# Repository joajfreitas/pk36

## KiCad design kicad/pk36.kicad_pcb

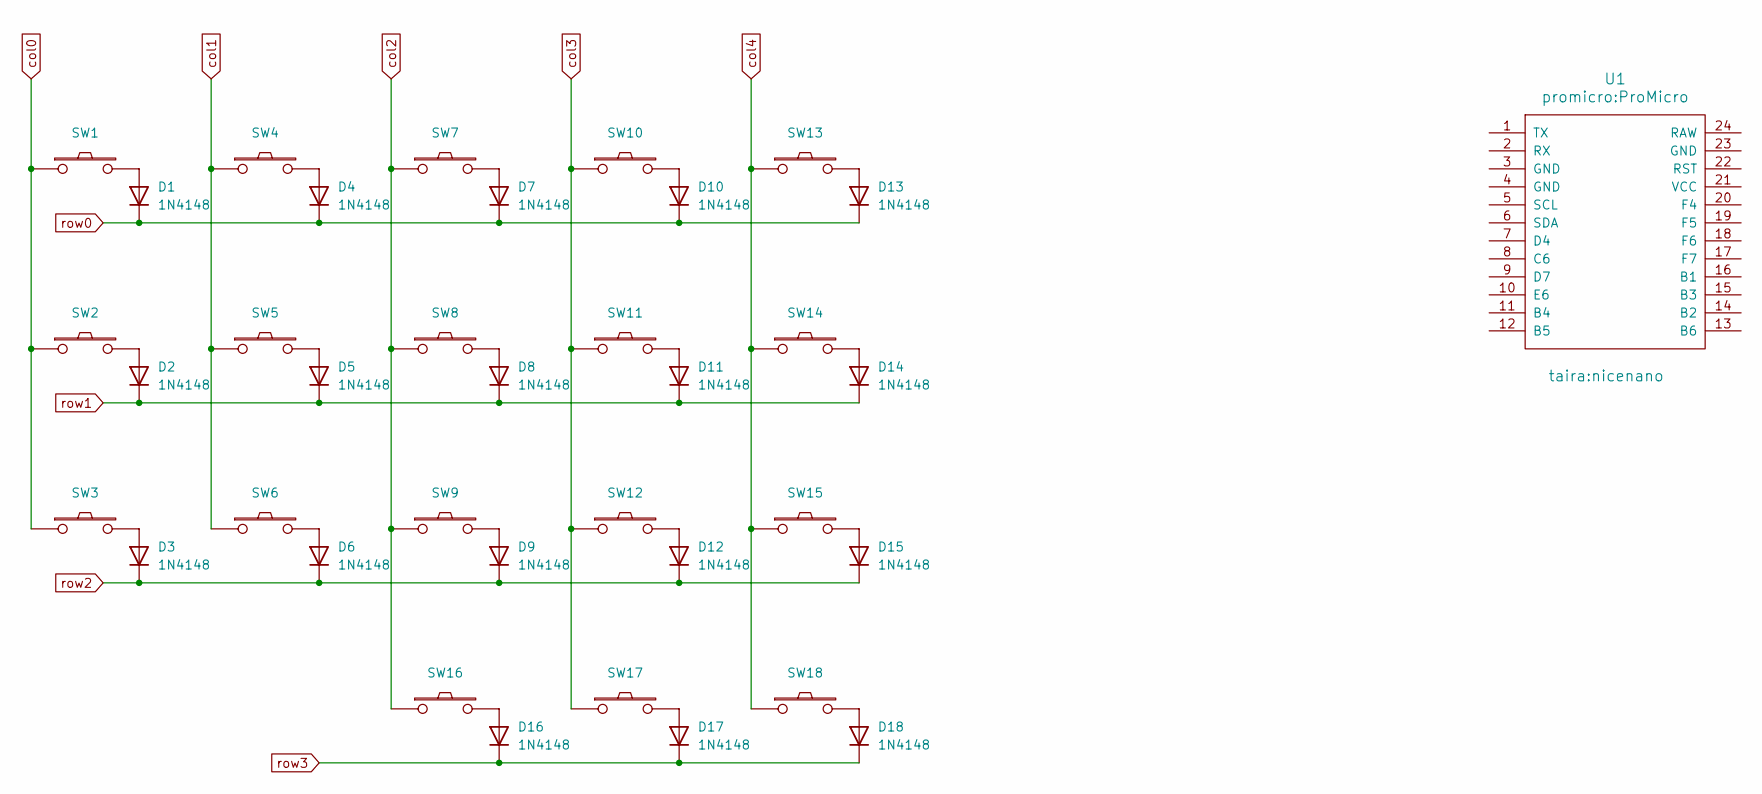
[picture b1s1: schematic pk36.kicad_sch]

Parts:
D1, D2, D3, D4, D5, D6, D7, D8, D9, D10, D11, D12, D13, D14, D15, D16, D17, D18: 1N4148; D_DO-35_SOD27_P7.62mm_Horizontal
SW1, SW2, SW3, SW4, SW5, SW6, SW7, SW8, SW9, SW10, SW11, SW12, SW13, SW14, SW15, SW16, SW17, SW18: ergodash:SW_PUSH; MX-ALPS-Choc-X-straight-crane
U1: promicro:ProMicro; nicenano

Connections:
unnamed: D1.2 (A), SW1.2
unnamed: D2.2 (A), SW2.2
unnamed: D3.2 (A), SW3.2
unnamed: D4.2 (A), SW4.2
unnamed: D5.2 (A), SW5.2
unnamed: D6.2 (A), SW6.2
unnamed: D7.2 (A), SW7.2
unnamed: D8.2 (A), SW8.2
unnamed: D9.2 (A), SW9.2
unnamed: D10.2 (A), SW10.2
unnamed: D11.2 (A), SW11.2
unnamed: D12.2 (A), SW12.2
unnamed: D13.2 (A), SW13.2
unnamed: D14.2 (A), SW14.2
unnamed: D15.2 (A), SW15.2
unnamed: D16.2 (A), SW16.2
unnamed: D17.2 (A), SW17.2
unnamed: D18.2 (A), SW18.2
col0: SW1.1, SW2.1, SW3.1
col1: SW4.1, SW5.1, SW6.1
col2: SW7.1, SW8.1, SW9.1, SW16.1
col3: SW10.1, SW11.1, SW12.1, SW17.1
col4: SW13.1, SW14.1, SW15.1, SW18.1
row0: D1.1 (K), D4.1 (K), D7.1 (K), D10.1 (K), D13.1 (K)
row1: D2.1 (K), D5.1 (K), D8.1 (K), D11.1 (K), D14.1 (K)
row2: D3.1 (K), D6.1 (K), D9.1 (K), D12.1 (K), D15.1 (K)
row3: D16.1 (K), D17.1 (K), D18.1 (K)

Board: 2 copper layers, 37 parts (0 on the bottom side), 27 nets, no tracks yet.

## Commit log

2023-06-20 Start pk36 repo
2023-10-08 Move kicad project
2023-10-08 Altium project

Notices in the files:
parts and their libraries:
Licensed under the MIT License - Copyright (c) 2020 foostan, Based on https://github.com/foostan/kbd/blob/master/kicad-footprints/kbd.pretty/ProMicro_v2.kicad_mod
